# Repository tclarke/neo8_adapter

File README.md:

# Breakout board for uBlock NEO-8 series. (NEO-8Q and NEO-M8)

This is a board designed to breakout pins on the uBlox NEO-8 GPS modules.
 - Solderless breadboard compatible
 - Edge-launch SMA for antenna and time pulse
 - Solder bridge to select UART or SPI
 - Solder bridge to enable/disable battery backup
 - Optional components for active (powered) antenna
 - Optional components for USB-C data
 - Optional components for USB-C power

## License
This design is licensed as [Open Source Hardware](http://www.oshwa.org/)

## Revision history
### Rev. 1
Initial revision of the board.

### Rev. 2
 - Add solder bridge documentation to the schematic
 - Add header pin labels to the PCB on the front and back
 - Tuning of solder mask markings for readability
 - Addition of solder mask markings to easily demarcate the optional sections

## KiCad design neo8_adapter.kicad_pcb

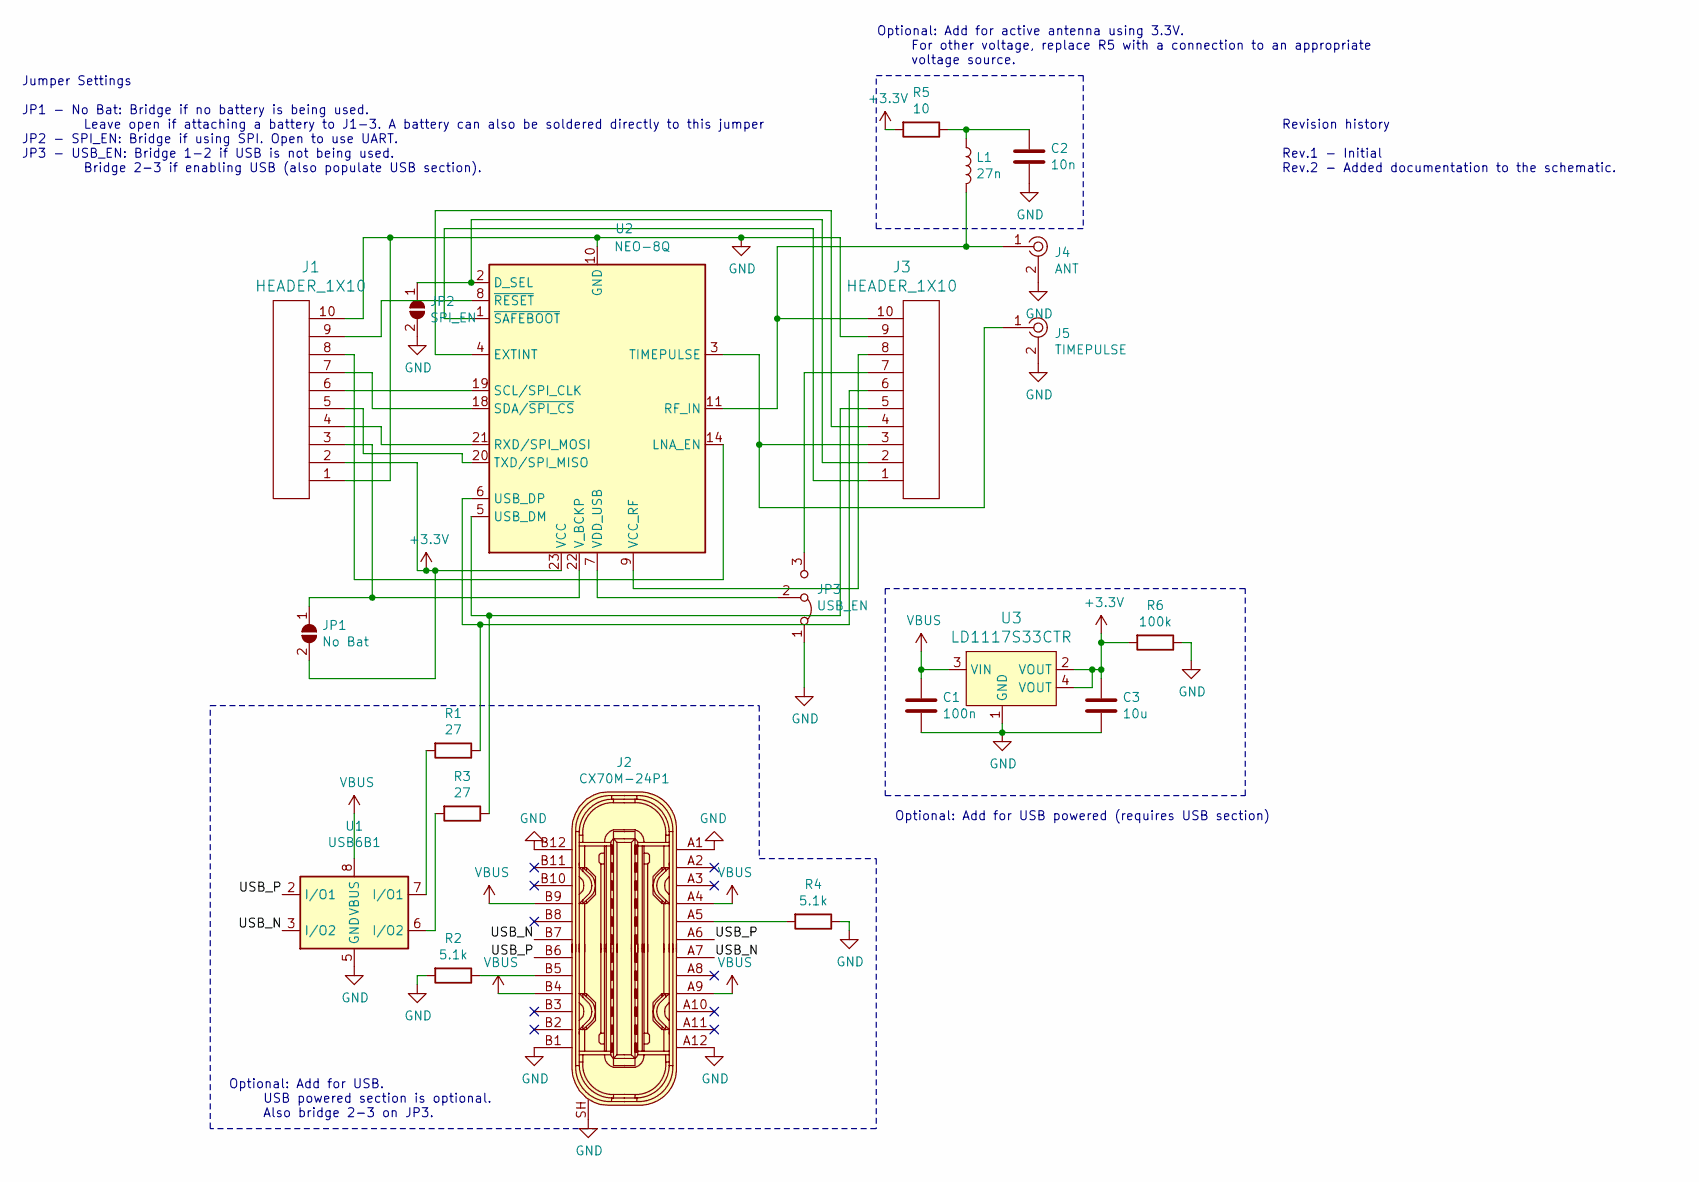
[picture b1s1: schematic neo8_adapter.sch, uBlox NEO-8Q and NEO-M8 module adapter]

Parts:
C1: 100n; C_0805_2012Metric_Pad1.15x1.40mm_HandSolder
C2: 10n; C_0805_2012Metric_Pad1.15x1.40mm_HandSolder
C3: 10u; C_0805_2012Metric_Pad1.15x1.40mm_HandSolder
J1, J3: HEADER_1X10; PinHeader_1x10_P2.54mm_Vertical
J2: CX70M-24P1; USB-C_Female_CX70M-24P1; MPN CX70M-24P1; Digi-Key_PN H125292CT-ND
J4: ANT; RF_SMA_BoardEdge_142-0701-801; MPN 142-0701-801; Digi-Key_PN J502-ND
J5: TIMEPULSE; RF_SMA_BoardEdge_142-0701-801; MPN 142-0701-801; Digi-Key_PN J502-ND
JP1: No Bat; SolderJumper-2_P1.3mm_Open_RoundedPad1.0x1.5mm
JP2: SPI_EN; SolderJumper-2_P1.3mm_Open_RoundedPad1.0x1.5mm
JP3: USB_EN; SolderJumper-3_P1.3mm_Bridged12_RoundedPad1.0x1.5mm_NumberL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
L1: 27n; L_0805_2012Metric_Pad1.15x1.40mm_HandSolder
R1, R3: 27; R_0805_2012Metric_Pad1.15x1.40mm_HandSolder
R2, R4: 5.1k; R_0805_2012Metric_Pad1.15x1.40mm_HandSolder
R5: 10; R_0805_2012Metric_Pad1.15x1.40mm_HandSolder
R6: 100k; R_0805_2012Metric_Pad1.15x1.40mm_HandSolder
U1: USB6B1; SOIC-8_3.9x4.9mm_P1.27mm
U2: NEO-8Q; ublox_NEO
U3: LD1117S33CTR; SOT-223; MPN LD1117S33CTR; Digi-Key_PN 497-1241-1-ND

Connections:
+3V3: C3.1, J1.2, JP1.2 (B), R5.2, R6.2, U2.23 (VCC), U3.2 (VOUT), U3.4 (VOUT)
/USB_N: J2.A7, J2.B7, U1.3 (I/O2)
/USB_P: J2.A6, J2.B6, U1.2 (I/O1)
GND: C1.2, C2.2, C3.2, J1.1, J1.10, J2.A1, J2.A12, J2.B1, J2.B12, J2.SH, J3.9, J4.2, J5.2, JP2.2 (B), JP3.1 (A), R2.2, R4.1, R6.1, U1.4 (GND), U1.5 (GND), U2.10 (GND), U2.12 (GND), U2.13 (GND), U2.24 (GND), U3.1 (GND)
unnamed: C2.1, L1.1, R5.1
unnamed: J1.3, JP1.1 (A), U2.22 (V_BCKP)
unnamed: J1.4, U2.21 (RXD/SPI_MOSI)
unnamed: J1.5, U2.20 (TXD/SPI_MISO)
unnamed: J1.6, U2.19 (SCL/SPI_CLK)
unnamed: J1.7, U2.18 (SDA/~SPI_CS)
unnamed: J1.8, U2.14 (LNA_EN)
unnamed: J1.9, U2.8 (~RESET)
unnamed: J2.A5, R4.2
unnamed: J2.B5, R2.1
unnamed: J3.1, U2.1 (~SAFEBOOT)
unnamed: J3.2, JP2.1 (A), U2.2 (D_SEL)
unnamed: J3.3, J5.1, U2.3 (TIMEPULSE)
unnamed: J3.4, U2.4 (EXTINT)
unnamed: J3.5, R3.1, U2.5 (USB_DM)
unnamed: J3.6, R1.1, U2.6 (USB_DP)
unnamed: J3.7, JP3.3 (B)
unnamed: J3.8, U2.9 (VCC_RF)
unnamed: J3.10, J4.1, L1.2, U2.11 (RF_IN)
unnamed: JP3.2 (C), U2.7 (VDD_USB)
unnamed: R1.2, U1.7 (I/O1)
unnamed: R3.2, U1.6 (I/O2)
VBUS: C1.1, J2.A4, J2.A9, J2.B4, J2.B9, U1.1 (VBUS), U1.8 (VBUS), U3.3 (VIN)

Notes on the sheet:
Optional: Add for active antenna using 3.3V. For other voltage, replace R5 with a connection to an appropriate voltage source.
Optional: Add for USB. USB powered section is optional. Also bridge 2-3 on JP3.
Optional: Add for USB powered (requires USB section)
Jumper Settings JP1 - No Bat: Bridge if no battery is being used. Leave open if attaching a battery to J1-3. A battery can also be soldered directly to this jumper JP2 - SPI_EN: Bridge if using SPI. Open to use UART. JP3 - USB_EN: Bridge 1-2 if USB is not being used. Bridge 2-3 if enabling USB (als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
Revision history Rev.1 - Initial Rev.2 - Added documentation to the schematic.

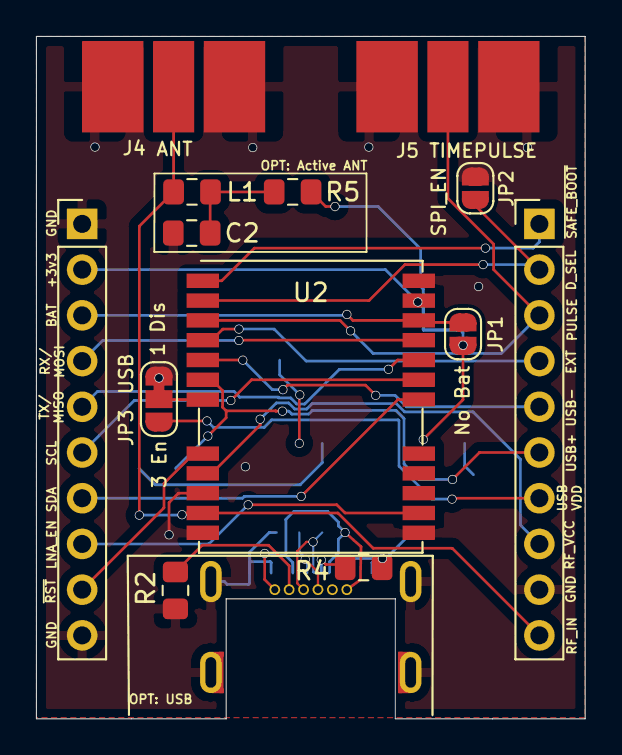
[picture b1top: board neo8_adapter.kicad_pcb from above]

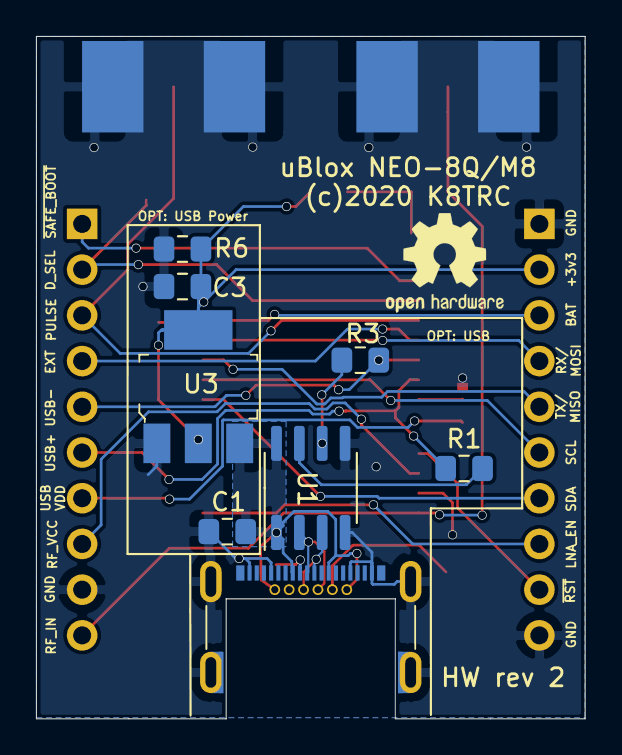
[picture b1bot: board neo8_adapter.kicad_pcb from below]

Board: 2 copper layers, 30.5 x 37.9 mm, 21 parts (8 on the bottom side), 27 nets.

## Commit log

2020-02-24 Initial checkin. Contains rev.2 schematic and pcb but rev.1 Gerbers
2020-02-24 Add a readme and associated board images

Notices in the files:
neo8_adapter.kicad_pcb:
(c)2020 K8TRC
